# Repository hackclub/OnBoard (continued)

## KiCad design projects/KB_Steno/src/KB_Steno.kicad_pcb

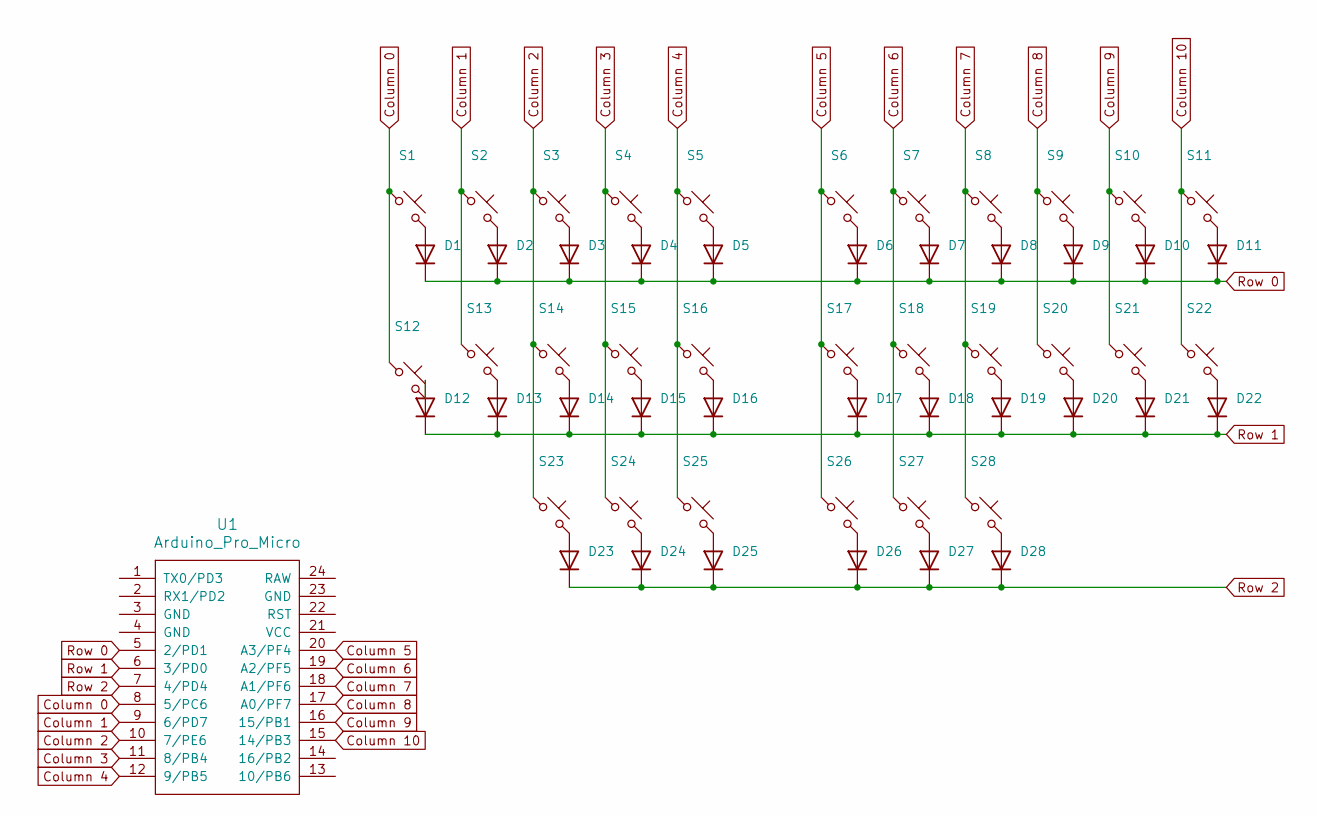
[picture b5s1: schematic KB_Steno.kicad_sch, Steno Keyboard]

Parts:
D1, D2, D3, D4, D5, D6, D7, D8, D9, D10, D11, D12, D13, D14, D15, D16, D17, D18, D19, D20, D21, D22, D23, D24, D25, D26, D27, D28: Diode; Diode_DO-35
S1, S2, S3, S4, S5, S6, S7, S8, S9, S10, S11, S12, S13, S14, S15, S16, S17, S18, S19, S20, S21, S22, S23, S24, S25, S26, S27, S28: Keyswitch; MX_PCB_1.00u
U1: Arduino_Pro_Micro

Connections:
Column 0: S1.1, S12.1, U1.8 (5/PC6)
Column 1: S2.1, S13.1, U1.9 (6/PD7)
Column 2: S3.1, S14.1, S23.1, U1.10 (7/PE6)
Column 3: S4.1, S15.1, S24.1, U1.11 (8/PB4)
Column 4: S5.1, S16.1, S25.1, U1.12 (9/PB5)
Column 5: S6.1, S17.1, S26.1, U1.20 (A3/PF4)
Column 6: S7.1, S18.1, S27.1, U1.19 (A2/PF5)
Column 7: S8.1, S19.1, S28.1, U1.18 (A1/PF6)
Column 8: S9.1, S20.1, U1.17 (A0/PF7)
Column 9: S10.1, S21.1, U1.16 (15/PB1)
Column 10: S11.1, S22.1, U1.15 (14/PB3)
unnamed: D1.2 (A), S1.2
unnamed: D2.2 (A), S2.2
unnamed: D3.2 (A), S3.2
unnamed: D4.2 (A), S4.2
unnamed: D5.2 (A), S5.2
unnamed: D6.2 (A), S6.2
unnamed: D7.2 (A), S7.2
unnamed: D8.2 (A), S8.2
unnamed: D9.2 (A), S9.2
unnamed: D10.2 (A), S10.2
unnamed: D11.2 (A), S11.2
unnamed: D12.2 (A), S12.2
unnamed: D13.2 (A), S13.2
unnamed: D14.2 (A), S14.2
unnamed: D15.2 (A), S15.2
unnamed: D16.2 (A), S16.2
unnamed: D17.2 (A), S17.2
unnamed: D18.2 (A), S18.2
unnamed: D19.2 (A), S19.2
unnamed: D20.2 (A), S20.2
unnamed: D21.2 (A), S21.2
unnamed: D22.2 (A), S22.2
unnamed: D23.2 (A), S23.2
unnamed: D24.2 (A), S24.2
unnamed: D25.2 (A), S25.2
unnamed: D26.2 (A), S26.2
unnamed: D27.2 (A), S27.2
unnamed: D28.2 (A), S28.2
Row 0: D1.1 (K), D2.1 (K), D3.1 (K), D4.1 (K), D5.1 (K), D6.1 (K), D7.1 (K), D8.1 (K), D9.1 (K), D10.1 (K), D11.1 (K), U1.5 (2/PD1)
Row 1: D12.1 (K), D13.1 (K), D14.1 (K), D15.1 (K), D16.1 (K), D17.1 (K), D18.1 (K), D19.1 (K), D20.1 (K), D21.1 (K), D22.1 (K), U1.6 (3/PD0)
Row 2: D23.1 (K), D24.1 (K), D25.1 (K), D26.1 (K), D27.1 (K), D28.1 (K), U1.7 (4/PD4)

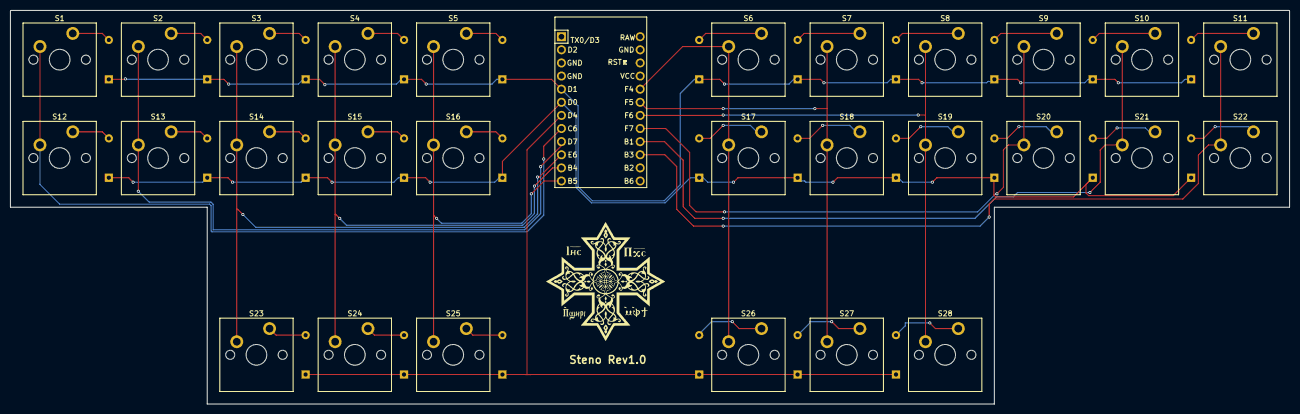
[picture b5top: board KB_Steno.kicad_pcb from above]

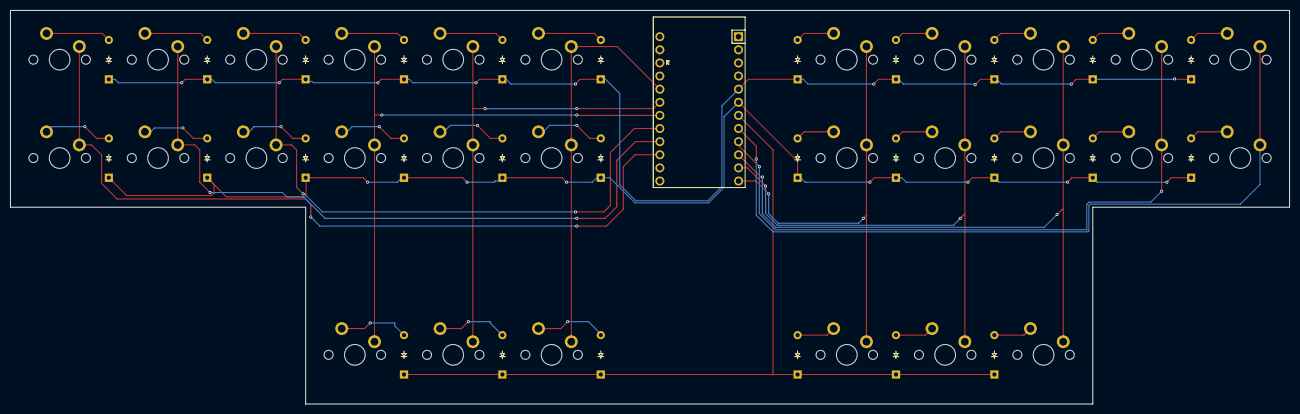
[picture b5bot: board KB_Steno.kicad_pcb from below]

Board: 2 copper layers, 247.7 x 76.2 mm, 57 parts (28 on the bottom side), 42 nets.

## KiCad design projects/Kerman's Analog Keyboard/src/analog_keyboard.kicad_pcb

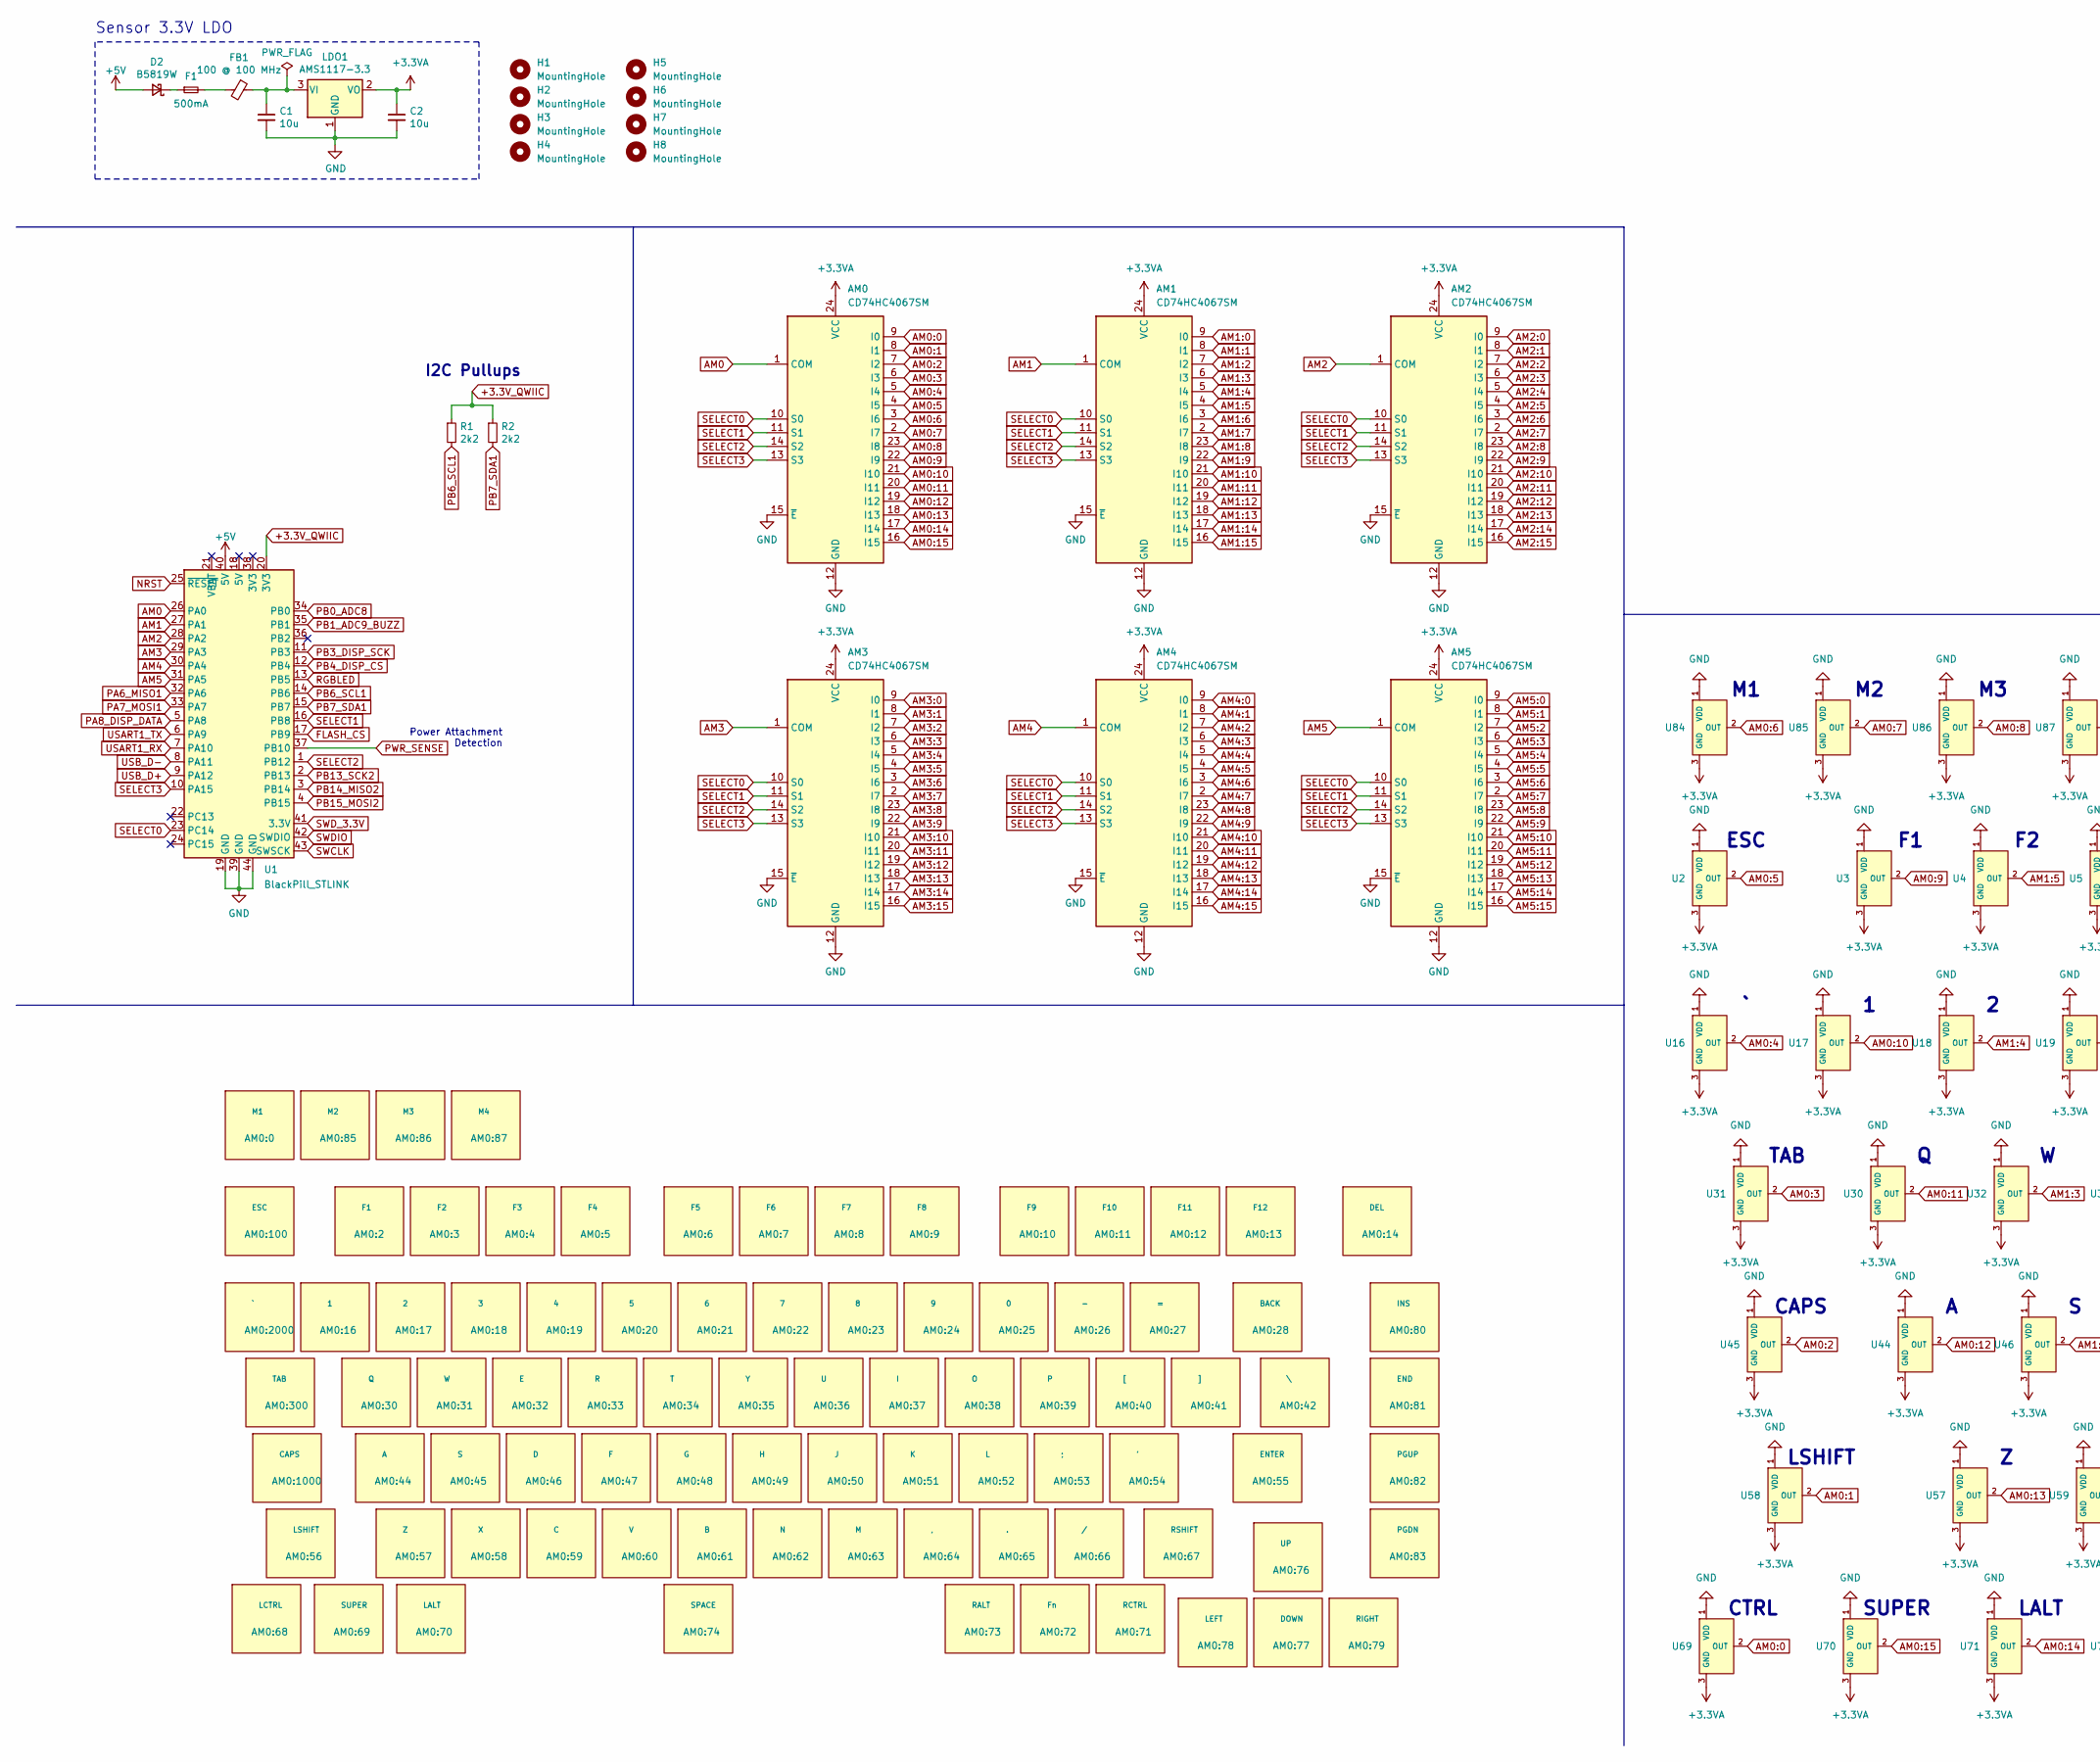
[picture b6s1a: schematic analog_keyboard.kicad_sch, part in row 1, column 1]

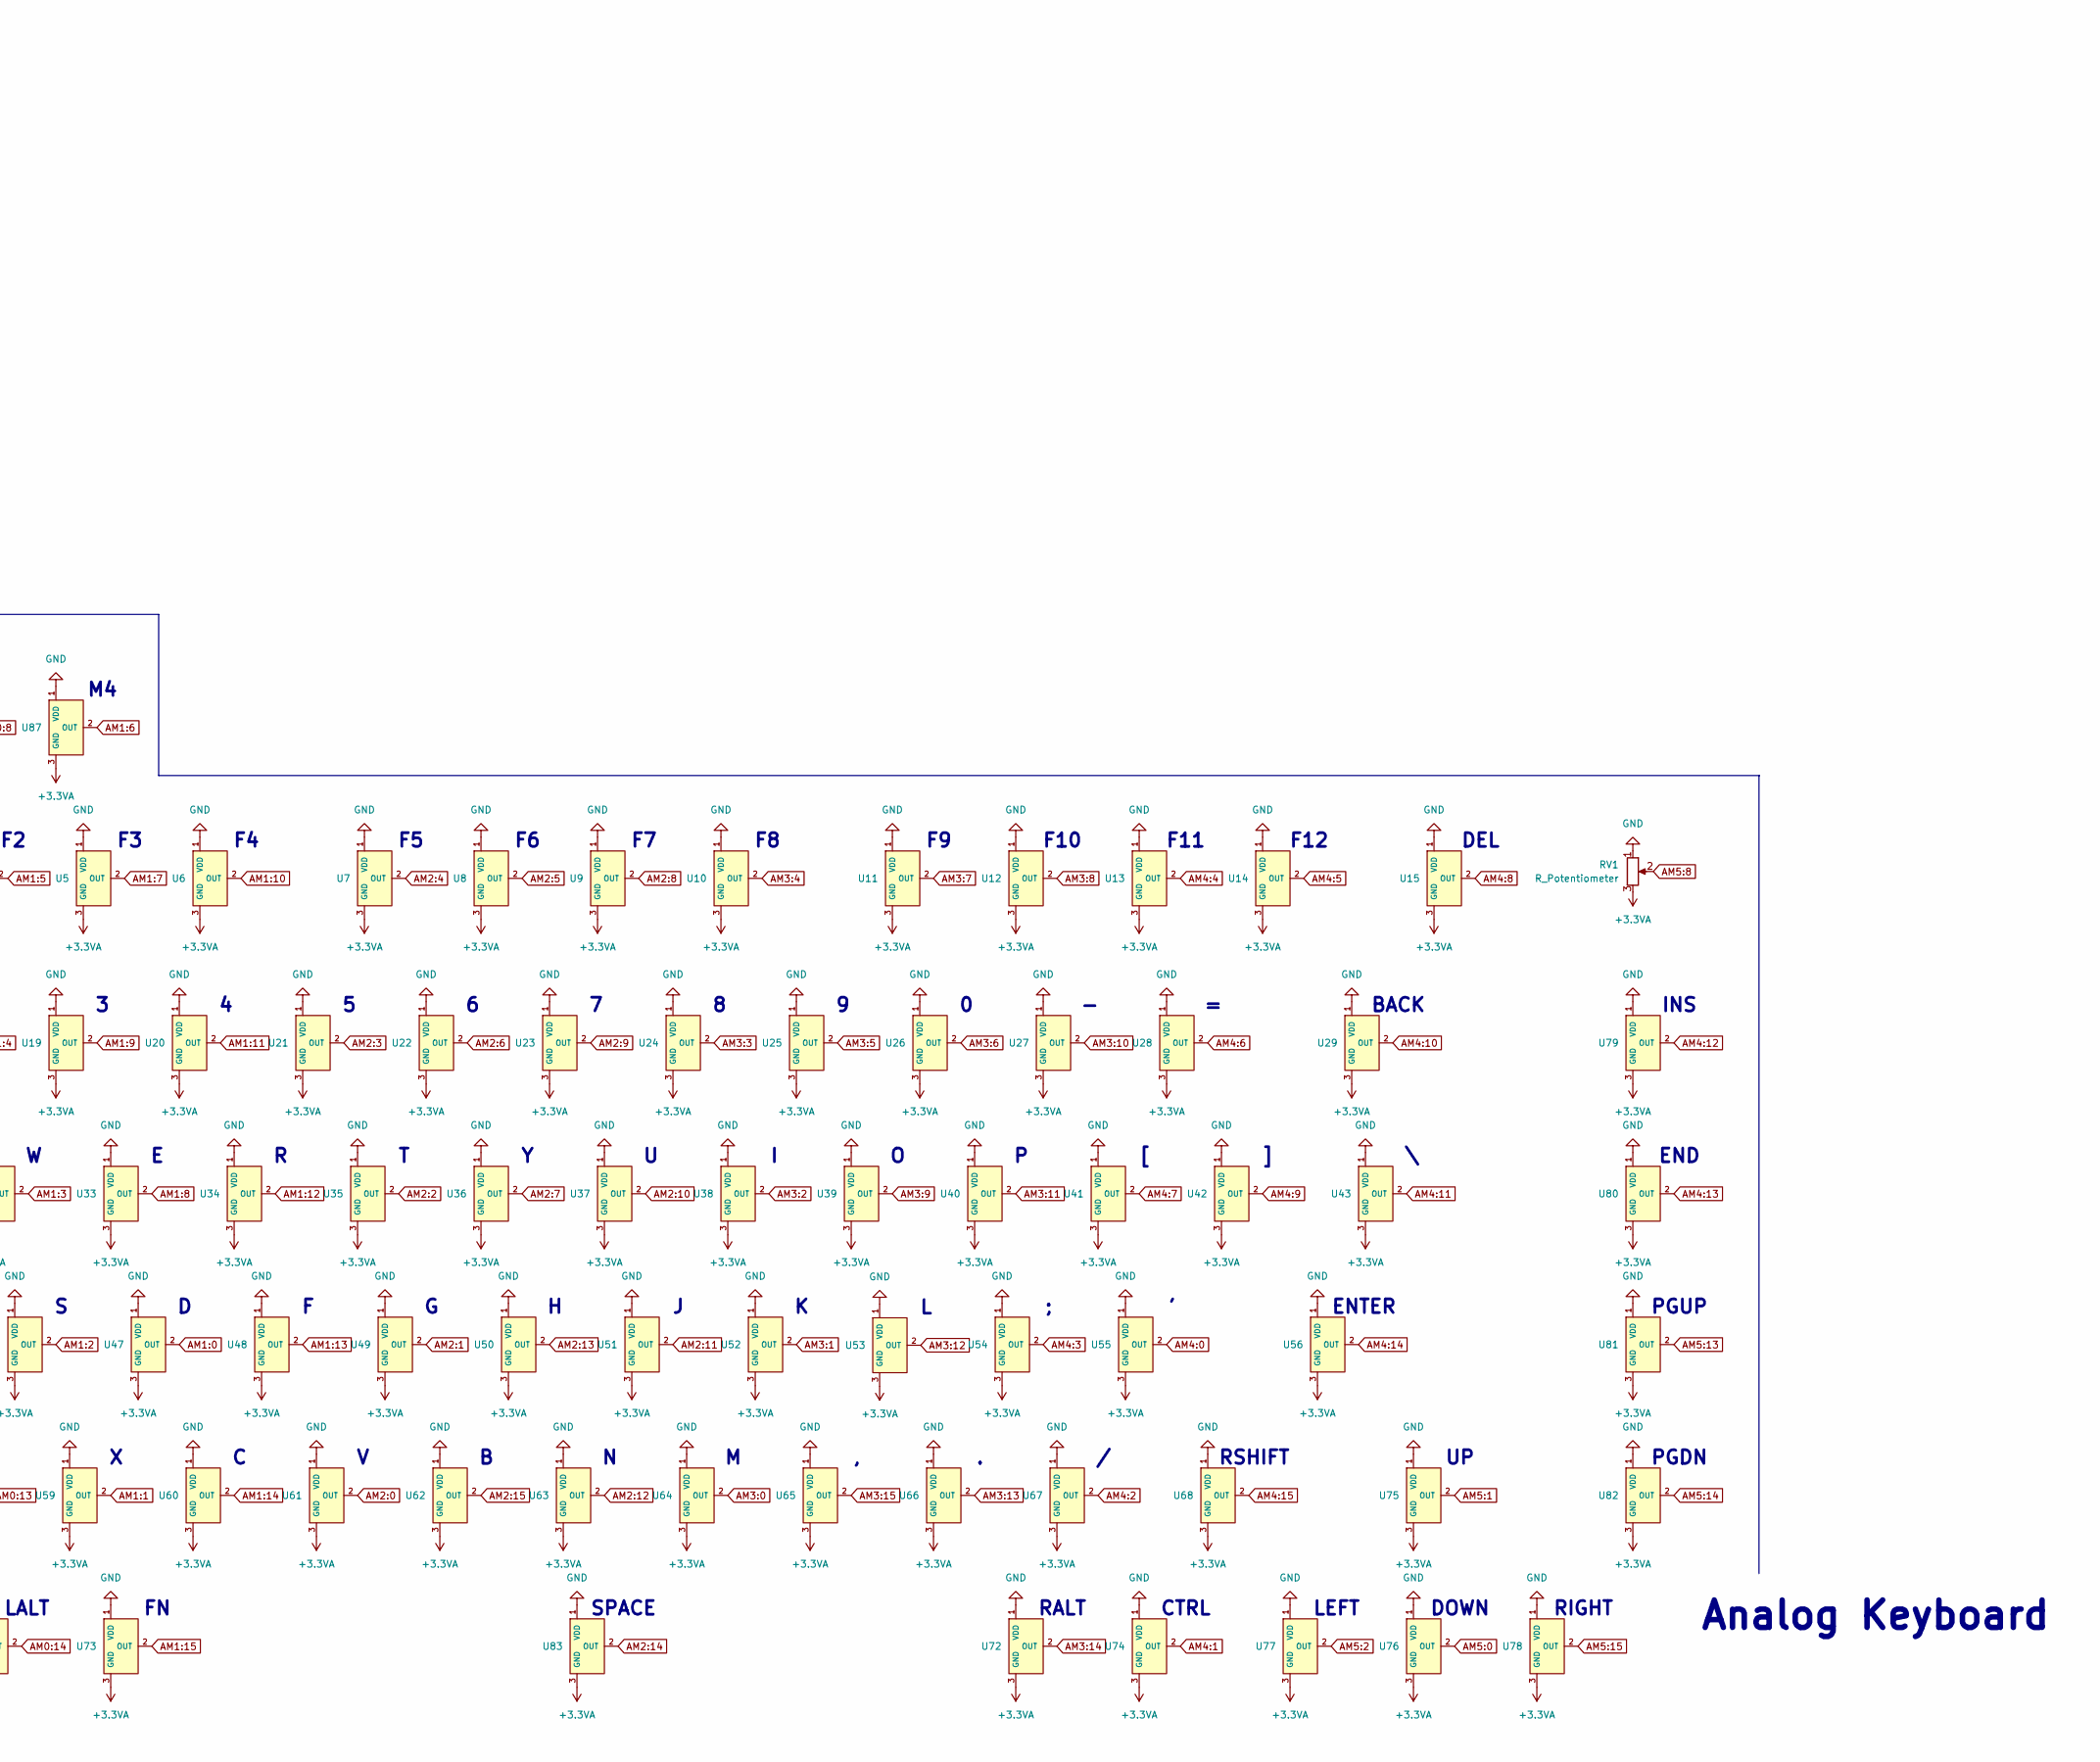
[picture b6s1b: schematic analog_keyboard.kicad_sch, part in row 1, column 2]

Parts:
AM0, AM1, AM2, AM3, AM4, AM5: CD74HC4067SM; SSOP-24_5.3x8.2mm_P0.65mm; LCSC Part C98457
AM0:0: M1; VoidSwitch_1u_SMD
AM0:2: F1; VoidSwitch_1u_SMD
AM0:3: F2; VoidSwitch_1u_SMD
AM0:4: F3; VoidSwitch_1u_SMD
AM0:5: F4; VoidSwitch_1u_SMD
AM0:6: F5; VoidSwitch_1u_SMD
AM0:7: F6; VoidSwitch_1u_SMD
AM0:8: F7; VoidSwitch_1u_SMD
AM0:9: F8; VoidSwitch_1u_SMD
AM0:10: F9; VoidSwitch_1u_SMD
AM0:11: F10; VoidSwitch_1u_SMD
AM0:12: F11; VoidSwitch_1u_SMD
AM0:13: F12; VoidSwitch_1u_SMD
AM0:14: DEL; VoidSwitch_1u_SMD
AM0:16: 1; VoidSwitch_1u_SMD
AM0:17: 2; VoidSwitch_1u_SMD
AM0:18: 3; VoidSwitch_1u_SMD
AM0:19: 4; VoidSwitch_1u_SMD
AM0:20: 5; VoidSwitch_1u_SMD
AM0:21: 6; VoidSwitch_1u_SMD
AM0:22: 7; VoidSwitch_1u_SMD
AM0:23: 8; VoidSwitch_1u_SMD
AM0:24: 9; VoidSwitch_1u_SMD
AM0:25: 0; VoidSwitch_1u_SMD
AM0:26: -; VoidSwitch_1u_SMD
AM0:27: =; VoidSwitch_1u_SMD
AM0:28: BACK; VoidSwitch_2u_SMD
AM0:30: Q; VoidSwitch_1u_SMD
AM0:31: W; VoidSwitch_1u_SMD
AM0:32: E; VoidSwitch_1u_SMD
AM0:33: R; VoidSwitch_1u_SMD
AM0:34: T; VoidSwitch_1u_SMD
AM0:35: Y; VoidSwitch_1u_SMD
AM0:36: U; VoidSwitch_1u_SMD
AM0:37: I; VoidSwitch_1u_SMD
AM0:38: O; VoidSwitch_1u_SMD
AM0:39: P; VoidSwitch_1u_SMD
AM0:40: [; VoidSwitch_1u_SMD
AM0:41: ]; VoidSwitch_1u_SMD
AM0:42: \; VoidSwitch_1.5u_SMD
AM0:44: A; VoidSwitch_1u_SMD
AM0:45: S; VoidSwitch_1u_SMD
AM0:46: D; VoidSwitch_1u_SMD
AM0:47: F; VoidSwitch_1u_SMD
AM0:48: G; VoidSwitch_1u_SMD
AM0:49: H; VoidSwitch_1u_SMD
AM0:50: J; VoidSwitch_1u_SMD
AM0:51: K; VoidSwitch_1u_SMD
AM0:52: L; VoidSwitch_1u_SMD
AM0:53: ;; VoidSwitch_1u_SMD
AM0:54: '; VoidSwitch_1u_SMD
AM0:55: ENTER; VoidSwitch_2.25u_SMD
AM0:56: LSHIFT; VoidSwitch_2.25u_SMD
AM0:57: Z; VoidSwitch_1u_SMD
AM0:58: X; VoidSwitch_1u_SMD
AM0:59: C; VoidSwitch_1u_SMD
AM0:60: V; VoidSwitch_1u_SMD
AM0:61: B; VoidSwitch_1u_SMD
AM0:62: N; VoidSwitch_1u_SMD
AM0:63: M; VoidSwitch_1u_SMD
AM0:64: ,; VoidSwitch_1u_SMD
AM0:65: .; VoidSwitch_1u_SMD
AM0:66: /; VoidSwitch_1u_SMD
AM0:67: RSHIFT; VoidSwitch_1.5u_SMD
AM0:68: LCTRL; VoidSwitch_1.25u_SMD
AM0:69: SUPER; VoidSwitch_1.25u_SMD
AM0:70: LALT; VoidSwitch_1.25u_SMD
AM0:71: RCTRL; VoidSwitch_1u_SMD
AM0:72: Fn; VoidSwitch_1u_SMD
AM0:73: RALT; VoidSwitch_1u_SMD
AM0:74: SPACE; VoidSwitch_6.25u_SMD
AM0:76: UP; VoidSwitch_1u_SMD
AM0:77: DOWN; VoidSwitch_1u_SMD
AM0:78: LEFT; VoidSwitch_1u_SMD
AM0:79: RIGHT; VoidSwitch_1u_SMD
AM0:80: INS; VoidSwitch_1u_SMD
AM0:81: END; VoidSwitch_1u_SMD
AM0:82: PGUP; VoidSwitch_1u_SMD
AM0:83: PGDN; VoidSwitch_1u_SMD
AM0:85: M2; VoidSwitch_1u_SMD
AM0:86: M3; VoidSwitch_1u_SMD
AM0:87: M4; VoidSwitch_1u_SMD
AM0:100: ESC; VoidSwitch_1u_SMD
AM0:300: TAB; VoidSwitch_1.5u_SMD
AM0:1000: CAPS; VoidSwitch_1.75u_SMD
AM0:2000: `; VoidSwitch_1u_SMD
C1, C2: 10u; C_0402_1005Metric; MPN CL05A106MQ5NUNC; LCSC Part C15525
D2: B5819W; D_SOD-123; MPN B5819W; LCSC Part C8598
F1: 500mA; Fuse_0603_1608Metric; LCSC Part C261937
FB1: 100 @ 100 MHz; L_0805_2012Metric; MPN GZ2012D101TF; LCSC Part C1015
H1, H2, H3, H4, H5, H6, H7, H8: MountingHole; MountingHole_3.2mm_M3_DIN965_Pad
LDO1: AMS1117-3.3; SOT-223-3_TabPin2; MPN AMS1117-3.3; LCSC Part C6186
R1, R2: 2k2; R_0402_1005Metric; MPN 0402WGF2201TCE; LCSC Part C25879
RV1: R_Potentiometer; Potentiometer_Alpha_RD901F-40-00D_Single_Vertical
U1: BlackPill_STLINK
U2, U3, U4, U5, U6, U7, U8, U9, U10, U11, U12, U13, U14, U15, U16, U17, U18, U19, U20, U21, U22, U23, U24, U25, U26, U27, U28, U29, U30, U31, U32, U33, U34, U35, U36, U37, U38, U39, U40, U41, U42, U43, U44, U45, U46, U47, U48, U49, U50, U51, U52, U53, U54, U55, U56, U57, U58, U59, U60, U61, U62, U63, U64, U65, U66, U67, U68, U69, U70, U71, U72, U73, U74, U75, U76, U77, U78, U79, U80, U81, U82, U83, U84, U85, U86, U87: Hall_Sensor; SOT-23; MPN GH39FKSW; LCSC Part C266230

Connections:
+3.3VA: AM0.24 (VCC), AM1.24 (VCC), AM2.24 (VCC), AM3.24 (VCC), AM4.24 (VCC), AM5.24 (VCC), C2.1, LDO1.2 (VO), RV1.3, U2.3 (GND), U3.3 (GND), U4.3 (GND), U5.3 (GND), U6.3 (GND), U7.3 (GND), U8.3 (GND), U9.3 (GND), U10.3 (GND), U11.3 (GND), U12.3 (GND), U13.3 (GND), U14.3 (GND), U15.3 (GND), U16.3 (GND), U17.3 (GND), U18.3 (GND), U19.3 (GND), U20.3 (GND), U21.3 (GND), U22.3 (GND), U23.3 (GND), U24.3 (GND), U25.3 (GND), U26.3 (GND), U27.3 (GND), U28.3 (GND), U29.3 (GND), U30.3 (GND), U31.3 (GND), U32.3 (GND), U33.3 (GND), U34.3 (GND), U35.3 (GND), U36.3 (GND), U37.3 (GND), U38.3 (GND), U39.3 (GND), U40.3 (GND), U41.3 (GND), U42.3 (GND), U43.3 (GND), U44.3 (GND), U45.3 (GND), U46.3 (GND), U47.3 (GND), U48.3 (GND), U49.3 (GND), U50.3 (GND), U51.3 (GND), U52.3 (GND), U53.3 (GND), U54.3 (GND), U55.3 (GND), U56.3 (GND), U57.3 (GND), U58.3 (GND), U59.3 (GND), U60.3 (GND), U61.3 (GND), U62.3 (GND), U63.3 (GND), U64.3 (GND), U65.3 (GND), U66.3 (GND), U67.3 (GND), U68.3 (GND), U69.3 (GND), U70.3 (GND), U71.3 (GND), U72.3 (GND), U73.3 (GND), U74.3 (GND), U75.3 (GND), U76.3 (GND), U77.3 (GND), U78.3 (GND), U79.3 (GND), U80.3 (GND), U81.3 (GND), U82.3 (GND), U83.3 (GND), U84.3 (GND), U85.3 (GND), U86.3 (GND), U87.3 (GND)
+3.3V_QWIIC: R1.1, R2.1, U1.20 (3V3)
+5V: D2.2 (A), U1.40 (5V)
AM0: AM0.1 (COM), U1.26 (PA0)
AM0:0: AM0.9 (I0), U69.2 (OUT)
AM0:1: AM0.8 (I1), U58.2 (OUT)
AM0:2: AM0.7 (I2), U45.2 (OUT)
AM0:3: AM0.6 (I3), U31.2 (OUT)
AM0:4: AM0.5 (I4), U16.2 (OUT)
AM0:5: AM0.4 (I5), U2.2 (OUT)
AM0:6: AM0.3 (I6), U84.2 (OUT)
AM0:7: AM0.2 (I7), U85.2 (OUT)
AM0:8: AM0.23 (I8), U86.2 (OUT)
AM0:9: AM0.22 (I9), U3.2 (OUT)
AM0:10: AM0.21 (I10), U17.2 (OUT)
AM0:11: AM0.20 (I11), U30.2 (OUT)
AM0:12: AM0.19 (I12), U44.2 (OUT)
AM0:13: AM0.18 (I13), U57.2 (OUT)
AM0:14: AM0.17 (I14), U71.2 (OUT)
AM0:15: AM0.16 (I15), U70.2 (OUT)
AM1: AM1.1 (COM), U1.27 (PA1)
AM1:0: AM1.9 (I0), U47.2 (OUT)
AM1:1: AM1.8 (I1), U59.2 (OUT)
AM1:2: AM1.7 (I2), U46.2 (OUT)
AM1:3: AM1.6 (I3), U32.2 (OUT)
AM1:4: AM1.5 (I4), U18.2 (OUT)
AM1:5: AM1.4 (I5), U4.2 (OUT)
AM1:6: AM1.3 (I6), U87.2 (OUT)
AM1:7: AM1.2 (I7), U5.2 (OUT)
AM1:8: AM1.23 (I8), U33.2 (OUT)
AM1:9: AM1.22 (I9), U19.2 (OUT)
AM1:10: AM1.21 (I10), U6.2 (OUT)
AM1:11: AM1.20 (I11), U20.2 (OUT)
AM1:12: AM1.19 (I12), U34.2 (OUT)
AM1:13: AM1.18 (I13), U48.2 (OUT)
AM1:14: AM1.17 (I14), U60.2 (OUT)
AM1:15: AM1.16 (I15), U73.2 (OUT)
AM2: AM2.1 (COM), U1.28 (PA2)
AM2:0: AM2.9 (I0), U61.2 (OUT)
AM2:1: AM2.8 (I1), U49.2 (OUT)
AM2:2: AM2.7 (I2), U35.2 (OUT)
AM2:3: AM2.6 (I3), U21.2 (OUT)
AM2:4: AM2.5 (I4), U7.2 (OUT)
AM2:5: AM2.4 (I5), U8.2 (OUT)
AM2:6: AM2.3 (I6), U22.2 (OUT)
AM2:7: AM2.2 (I7), U36.2 (OUT)
AM2:8: AM2.23 (I8), U9.2 (OUT)
AM2:9: AM2.22 (I9), U23.2 (OUT)
AM2:10: AM2.21 (I10), U37.2 (OUT)
AM2:11: AM2.20 (I11), U51.2 (OUT)
AM2:12: AM2.19 (I12), U63.2 (OUT)
AM2:13: AM2.18 (I13), U50.2 (OUT)
AM2:14: AM2.17 (I14), U83.2 (OUT)
AM2:15: AM2.16 (I15), U62.2 (OUT)
AM3: AM3.1 (COM), U1.29 (PA3)
AM3:0: AM3.9 (I0), U64.2 (OUT)
AM3:1: AM3.8 (I1), U52.2 (OUT)
AM3:2: AM3.7 (I2), U38.2 (OUT)
AM3:3: AM3.6 (I3), U24.2 (OUT)
AM3:4: AM3.5 (I4), U10.2 (OUT)
AM3:5: AM3.4 (I5), U25.2 (OUT)
AM3:6: AM3.3 (I6), U26.2 (OUT)
AM3:7: AM3.2 (I7), U11.2 (OUT)
AM3:8: AM3.23 (I8), U12.2 (OUT)
AM3:9: AM3.22 (I9), U39.2 (OUT)
AM3:10: AM3.21 (I10), U27.2 (OUT)
AM3:11: AM3.20 (I11), U40.2 (OUT)
AM3:12: AM3.19 (I12), U53.2 (OUT)
AM3:13: AM3.18 (I13), U66.2 (OUT)
AM3:14: AM3.17 (I14), U72.2 (OUT)
AM3:15: AM3.16 (I15), U65.2 (OUT)
AM4: AM4.1 (COM), U1.30 (PA4)
AM4:0: AM4.9 (I0), U55.2 (OUT)
AM4:1: AM4.8 (I1), U74.2 (OUT)
AM4:2: AM4.7 (I2), U67.2 (OUT)
AM4:3: AM4.6 (I3), U54.2 (OUT)
AM4:4: AM4.5 (I4), U13.2 (OUT)
AM4:5: AM4.4 (I5), U14.2 (OUT)
AM4:6: AM4.3 (I6), U28.2 (OUT)
AM4:7: AM4.2 (I7), U41.2 (OUT)
AM4:8: AM4.23 (I8), U15.2 (OUT)
AM4:9: AM4.22 (I9), U42.2 (OUT)
AM4:10: AM4.21 (I10), U29.2 (OUT)
AM4:11: AM4.20 (I11), U43.2 (OUT)
AM4:12: AM4.19 (I12), U79.2 (OUT)
AM4:13: AM4.18 (I13), U80.2 (OUT)
AM4:14: AM4.17 (I14), U56.2 (OUT)
AM4:15: AM4.16 (I15), U68.2 (OUT)
AM5: AM5.1 (COM), U1.31 (PA5)
AM5:0: AM5.9 (I0), U76.2 (OUT)
AM5:1: AM5.8 (I1), U75.2 (OUT)
AM5:2: AM5.7 (I2), U77.2 (OUT)
AM5:3: AM5.6 (I3)
AM5:4: AM5.5 (I4)
AM5:5: AM5.4 (I5)
AM5:6: AM5.3 (I6)
AM5:7: AM5.2 (I7)
AM5:8: AM5.23 (I8), RV1.2
AM5:9: AM5.22 (I9)
AM5:10: AM5.21 (I10)
AM5:11: AM5.20 (I11)
AM5:12: AM5.19 (I12)
AM5:13: AM5.18 (I13), U81.2 (OUT)
AM5:14: AM5.17 (I14), U82.2 (OUT)
AM5:15: AM5.16 (I15), U78.2 (OUT)
FLASH_CS: U1.17 (PB9)
GND: AM0.12 (GND), AM0.15 (~E), AM1.12 (GND), AM1.15 (~E), AM2.12 (GND), AM2.15 (~E), AM3.12 (GND), AM3.15 (~E), AM4.12 (GND), AM4.15 (~E), AM5.12 (GND), AM5.15 (~E), C1.2, C2.2, LDO1.1 (GND), RV1.1, U1.19 (GND), U1.39 (GND), U1.44 (GND), U2.1 (VDD), U3.1 (VDD), U4.1 (VDD), U5.1 (VDD), U6.1 (VDD), U7.1 (VDD), U8.1 (VDD), U9.1 (VDD), U10.1 (VDD), U11.1 (VDD), U12.1 (VDD), U13.1 (VDD), U14.1 (VDD), U15.1 (VDD), U16.1 (VDD), U17.1 (VDD), U18.1 (VDD), U19.1 (VDD), U20.1 (VDD), U21.1 (VDD), U22.1 (VDD), U23.1 (VDD), U24.1 (VDD), U25.1 (VDD), U26.1 (VDD), U27.1 (VDD), U28.1 (VDD), U29.1 (VDD), U30.1 (VDD), U31.1 (VDD), U32.1 (VDD), U33.1 (VDD), U34.1 (VDD), U35.1 (VDD), U36.1 (VDD), U37.1 (VDD), U38.1 (VDD), U39.1 (VDD), U40.1 (VDD), U41.1 (VDD), U42.1 (VDD), U43.1 (VDD), U44.1 (VDD), U45.1 (VDD), U46.1 (VDD), U47.1 (VDD), U48.1 (VDD), U49.1 (VDD), U50.1 (VDD), U51.1 (VDD), U52.1 (VDD), U53.1 (VDD), U54.1 (VDD), U55.1 (VDD), U56.1 (VDD), U57.1 (VDD), U58.1 (VDD), U59.1 (VDD), U60.1 (VDD), U61.1 (VDD), U62.1 (VDD), U63.1 (VDD), U64.1 (VDD), U65.1 (VDD), U66.1 (VDD), U67.1 (VDD), U68.1 (VDD), U69.1 (VDD), U70.1 (VDD), U71.1 (VDD), U72.1 (VDD), U73.1 (VDD), U74.1 (VDD), U75.1 (VDD), U76.1 (VDD), U77.1 (VDD), U78.1 (VDD), U79.1 (VDD), U80.1 (VDD), U81.1 (VDD), U82.1 (VDD), U83.1 (VDD), U84.1 (VDD), U85.1 (VDD), U86.1 (VDD), U87.1 (VDD)
NRST: U1.25 (~RESET)
unnamed: D2.1 (K), F1.1
unnamed: F1.2, FB1.2
unnamed: C1.1, FB1.1, LDO1.3 (VI)
PA6_MISO1: U1.32 (PA6)
PA7_MOSI1: U1.33 (PA7)
PA8_DISP_DATA: U1.5 (PA8)
PB0_ADC8: U1.34 (PB0)
PB1_ADC9_BUZZ: U1.35 (PB1)
PB3_DISP_SCK: U1.11 (PB3)
PB4_DISP_CS: U1.12 (PB4)
PB6_SCL1: R1.2, U1.14 (PB6)
PB7_SDA1: R2.2, U1.15 (PB7)
PB13_SCK2: U1.2 (PB13)
PB14_MISO2: U1.3 (PB14)
PB15_MOSI2: U1.4 (PB15)
PWR_SENSE: U1.37 (PB10)
RGBLED: U1.13 (PB5)
SELECT0: AM0.10 (S0), AM1.10 (S0), AM2.10 (S0), AM3.10 (S0), AM4.10 (S0), AM5.10 (S0), U1.23 (PC14)
SELECT1: AM0.11 (S1), AM1.11 (S1), AM2.11 (S1), AM3.11 (S1), AM4.11 (S1), AM5.11 (S1), U1.16 (PB8)
SELECT2: AM0.14 (S2), AM1.14 (S2), AM2.14 (S2), AM3.14 (S2), AM4.14 (S2), AM5.14 (S2), U1.1 (PB12)
SELECT3: AM0.13 (S3), AM1.13 (S3), AM2.13 (S3), AM3.13 (S3), AM4.13 (S3), AM5.13 (S3), U1.10 (PA15)
SWCLK: U1.43 (SWSCK)
SWDIO: U1.42 (SWDIO)
SWD_3.3V: U1.41 (3.3V)
USART1_RX: U1.7 (PA10)
USART1_TX: U1.6 (PA9)
USB_D+: U1.9 (PA12)
USB_D-: U1.8 (PA11)

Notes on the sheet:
I2C Pullups
PGUP
Power Attachment Detection
PGDN
INS
BACK
LEFT
Analog Keyboard
DOWN
DEL
RSHIFT
CTRL
SPACE
LSHIFT
CAPS
Sensor 3.3V LDO
F11
RALT
F12
TAB
SUPER
END
ESC
RIGHT
F10
LALT
ENTER

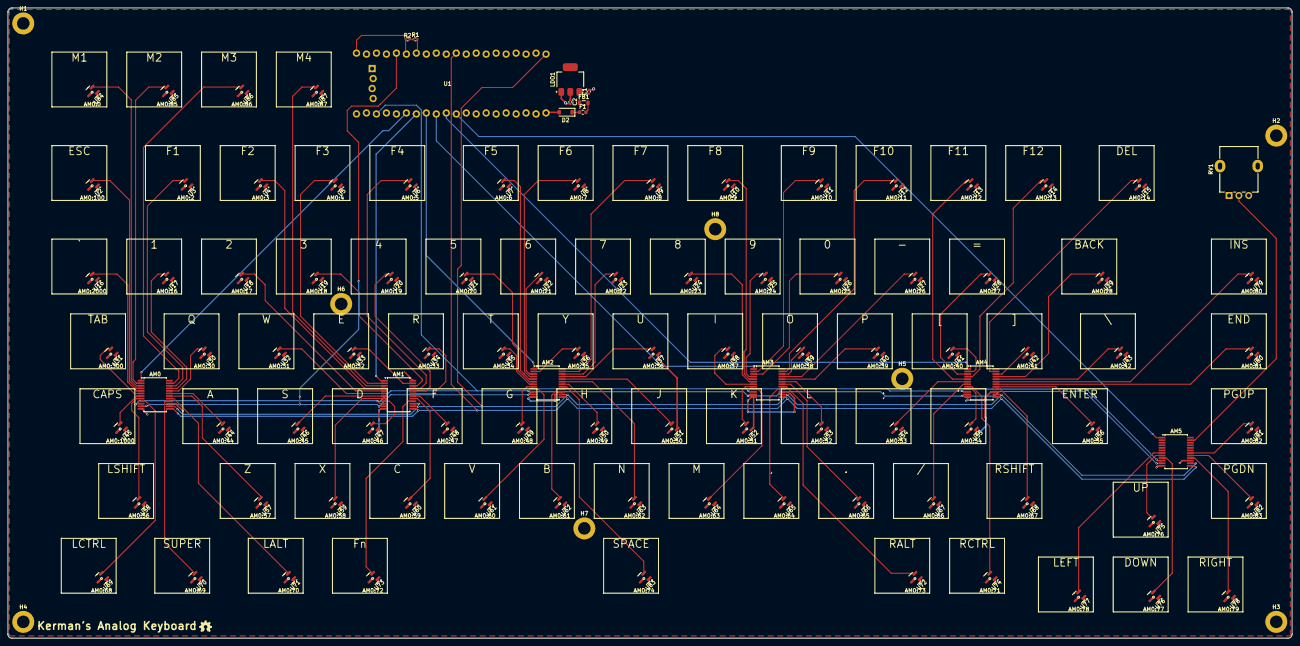
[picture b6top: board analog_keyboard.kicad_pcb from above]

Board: 2 copper layers, 327.0 x 160.5 mm, 196 parts (0 on the bottom side), 106 nets.
